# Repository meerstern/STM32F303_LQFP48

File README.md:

# STM32F303_LQFP48

The Converter board of Kicad Files for STM32F303-LQFP48

STM32F303 LQFP48を2.54mmピッチへ変換します。  
5列両側の一般的なブレッドボードで両側に1つ空きが出るサイズです。  
Nucleo等の評価ボードが発売されていない48ピンICの変換基板です。  
32ピンではRAMサイズやピン数が足りないが、64ピンでは多すぎるという方にお勧めです。  
※mbedには対応していません。 

## 仕様
  * MPU48ピンの全ピンにアクセス可能です。
  * 両側それぞれ20ピン、計40ピンです。
  * VDD及びVDDはそれぞれ1つのピンにまとめています。
  * アナログピンはVSSA、VDDAをジャンパするとVDDとVSSからそれぞれ供給されます。
  * VDDへ電源を供給するとLED1が点灯します。
  * SWDピンが出ているため、STLinkで接続して書き込みします。
  * SWDピンはNucleo等のSTLinkのピン配置と同じ順序です。
  * BOOT0のピンヘッダがあり、簡単にモード切り替え可能です。
  * タクトスイッチを取り付けることでリセットボタンが実装可能です。

## 使用可能MPU
  * STM32F303C8XX ROM64KB,  RAM12KB  [Digikey Link][1]
  * STM32F303CCXX ROM256KB, RAM40KB  [Digikey Link][3]
  ※上記の全MPUで動作確認している訳ではありません。  

[1]: http://www.digikey.jp/product-detail/ja/stmicroelectronics/STM32F303C8T6/497-15198-ND/5051326 "*1"
[3]: http://www.digikey.jp/product-detail/ja/stmicroelectronics/STM32F303CCT6/497-13318-ND/3660423 "*3"

## 書き込み方法/使用方法
  * アナログピンはVSSA、VDDAをジャンパさせます。
  * BOOTピンを0へセットします。
  * SWDピンが出ているため、STLinkで接続して書き込みします。
  * SWDピンはNucleo等のSTLinkのピン配置と同じ順序です。
  * 電源を供給し、NucleoやSTLinkV2プログラマ等を使用してSTLinkUtility等から書き込んでください。  

License - MIT

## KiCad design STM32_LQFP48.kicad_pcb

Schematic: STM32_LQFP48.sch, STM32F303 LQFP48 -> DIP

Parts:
C1, C2, C3, C4, C5, C6, C7: CAPACITOR1608; generic-SMD1608
JP1: PINHD-1X5; pinhead-1X05
JP2: PINHD-1X3; pinhead-1X03
JP3, JP5: PINHD-1X2; pinhead-1X02
JP4, JP6: PINHD-1X20; pinhead-1X20
LED1: LED1608; generic-LED1608
R1, R2: RESISTOR1608; generic-SMD1608
S1: 10-XX; switch-omron-B3F-10XX
U1: STM32F303; LQFP-48_7x7mm_Pitch0.5mm
X1: CRYSTAL_SMD; pinhead-1X03

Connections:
BOOT: JP2.2, U1.44 (BOOT0)
NRST: C3.1, JP1.5, S1.1, S1.2, U1.7 (~NRST)
unnamed: JP2.1, R2.2
unnamed: LED1.K, R1.1
OSCI: C1.1, JP4.7, U1.5 (OSC_IN), X1.1
OSCO: C2.1, JP4.8, U1.6 (OSC_OUT), X1.2
PA0: JP4.9, U1.10 (WKUP/USART2_CTS/ADC1_IN0/TIM2_CH1_ETR/P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)
PA1: JP4.10, U1.11 (USART2_RTS/ADC1_IN1/TIM2_CH2/PA1)
PA2: JP4.11, U1.12 (USART2_TX/ADC1_IN2/TIM2_CH3/TIM15_CH1/P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)
PA3: JP4.12, U1.13 (USART2_RX/ADC1_IN3/TIM2_CH4/TIM15_CH2/P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)
PA4: JP4.13, U1.14 (SPI1_NSS/ADC1_IN4/USART2_CK/DAC1_OUT/PA4)
PA5: JP4.14, U1.15 (SPI1_SCK/ADC1_IN5/DAC2_OUT/PA5)
PA6: JP4.15, U1.16 (SPI1_MISO/ADC1_IN6/TIM3_CH1/PA6)
PA7: JP4.16, U1.17 (SPI1_MOSI/ADC1_IN7/TIM3_CH2/PA7)
PA8: JP6.15, U1.29 (USART1_CK/MCO/TIM1_CH1/PA8)
PA9: JP6.14, U1.30 (USART1_TX/TIM1_CH2/TIM15_BKIN/PA9)
PA10: JP6.13, U1.31 (USART1_RX/TIM1_CH3/TIM17_BKIN/PA10)
PA11: JP6.12, U1.32 (USART1_CTS/TIM1_CH4/PA11)
PA12: JP6.11, U1.33 (USART1_RTS/TIM1_ETR/PA12)
PA13: JP1.4, JP6.10, U1.34 (JTMS/SWDIO/PA13)
PA14: JP1.2, JP6.9, U1.37 (JTCK/SWCLK/PA14)
PA15: JP6.8, U1.38 (JTDI/PA15)
PB0: JP4.17, U1.18 (PB0/ADC1_IN8/TIM3_CH3)
PB1: JP4.18, U1.19 (PB1/ADC1_IN9/TIM3_CH4)
PB2: JP4.19, U1.20 (PB2/BOOT1)
PB3: JP6.7, U1.39 (PB3/JTDO)
PB4: JP6.6, U1.40 (PB4/NJRST)
PB5: JP6.5, U1.41 (PB5/I2C1_SMBA/TIM16_BKIN)
PB6: JP6.4, U1.42 (PB6/I2C1_SCL/TIM4_CH1/TIM16_CH1N)
PB7: JP6.3, U1.43 (PB7/I2C1_SDA/TIM17_CH1N/TIM4_CH2)
PB8: JP6.2, U1.45 (PB8/TIM4_CH3/TIM16_CH1/CEC)
PB9: JP6.1, U1.46 (PB9/TIM4_CH4/TIM17_CH1)
PB10: JP4.20, U1.21 (PB10/I2C2_SCL/USART3_TX)
PB11: JP6.20, U1.22 (PB11/I2C2_SDA/USART3_RX)
PB12: JP6.19, U1.25 (PB12/SPI2_NSS/I2C2_SMBA/TIM1_BKIN/USART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)
PB13: JP6.18, U1.26 (PB13/SPI2_SCK/TIM1_CH1N/USART3_CTS)
PB14: JP6.17, U1.27 (PB14/SPI2_MISO/TIM1_CH2N/USART3_RTS)
PB15: JP6.16, U1.28 (PB15/SPI2_MOSI/TIM1_CH3N/TIM15_CH1N)
PC13: JP4.4, U1.2 (PC13/TAMPER_RTC)
PC14: JP4.5, U1.3 (PC14/OSC32_IN)
PC15: JP4.6, U1.4 (PC15/OSC32_OUT)
VBAT: JP4.3, U1.1 (VBAT)
VDD: C4.1, C6.1, C7.1, JP1.1, JP3.1, JP4.1, LED1.A, R2.1, U1.24 (VDD), U1.36 (VDD), U1.48 (VDD)
VDDA: C5.1, JP3.2, U1.9 (VDDA)
VSS: C1.2, C2.2, C3.2, C4.2, C5.2, C6.2, C7.2, JP1.3, JP2.3, JP4.2, JP5.1, R1.2, S1.3, S1.4, U1.23 (VSS), U1.35 (VSS), U1.47 (VSS), X1.3
VSSA: JP5.2, U1.8 (VSSA)

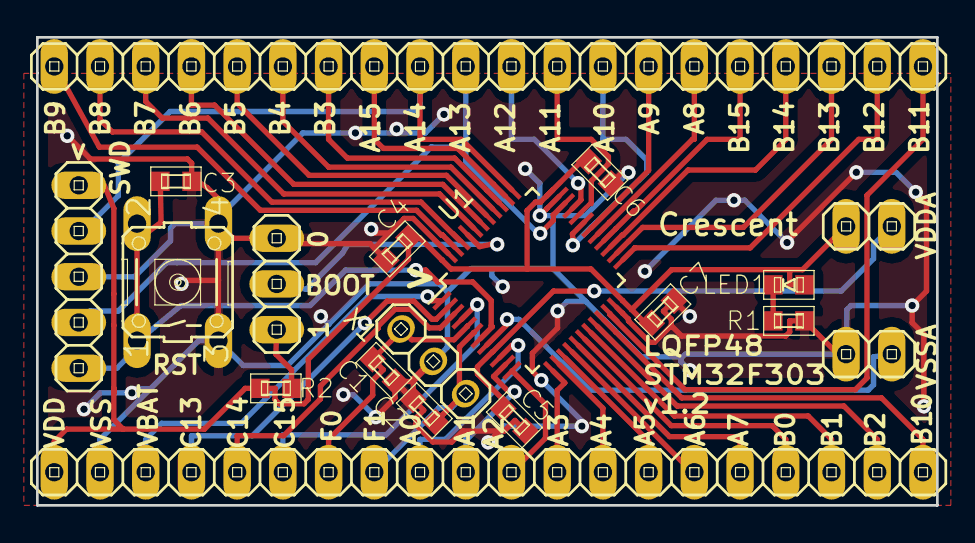
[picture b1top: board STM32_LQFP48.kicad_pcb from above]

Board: 2 copper layers, 50.0 x 26.0 mm, 19 parts (0 on the bottom side), 46 nets.

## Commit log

2017-01-03 Init
2017-01-09 ADD PDF and LibFile
2017-01-22 Minor Fix of Back Mask
2017-05-28 Add swd figure
